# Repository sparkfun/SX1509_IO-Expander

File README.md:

SparkFun 16 Output I/O Expander Breakout - SX1509
======================================

[  
*SX1509 16 Output I/O Expander Breakout (BOB-13601)*](https://www.sparkfun.com/products/13601)

The SX1509 16 Output I/O Expander Breakout Board makes it easy to prototype using the SX1509 so you can add more I/O onto your Arduino or I/O limited controller. It can leverage your I2C interface for 16 extra channels of GPIO and contains a fully programmable LED driver and a keypad scanning engine which enables continuous keypad monitoring of up to 64 keys. Since the I/O banks can operate between 1.2V and 3.6V (5.5V tolerant) independent of both the core and each other, this device can also work as a level-shifter.

Features include:

* 16 channels of bi-directional I/O - Pull-up/down resistors, push/pull or open-drain outputs, programmable polarity.
* 5.5V tolerant I/O's (1.2-3.6V operating voltage)
* LED Driver: PWM and blink control on all I/O's, breathe capability on a select few.
* Level shifting I/O's: Independent I/O rails (VCC1, VCC2) allow for up/down level shifting.
* Keypad scanning engine: Supports up to 64 keys (in an 8x8 matrix configuration).

Repository Contents
-------------------
* **/Hardware** - Eagle design files (.brd, .sch)
* **/Libraries** - Libraries for use with the <PRODUCT NAME>
* **/Production** - Production panel files (.brd)

Documentation
--------------
* **[Library](https://github.com/sparkfun/SparkFun_SX1509_Arduino_Library)** - <LANGUAGE> library for the SX1509.
* **[Hookup Guide](https://learn.sparkfun.com/tutorials/sx1509-io-expander-breakout-hookup-guide?_ga=1.227875988.863167751.1453149924)** - Basic hookup guide for the SX1509.
* **[SparkFun Fritzing repo](https://github.com/sparkfun/Fritzing_Parts)** - Fritzing diagrams for SparkFun products.
* **[SparkFun 3D Model repo](https://github.com/sparkfun/3D_Models)** - 3D models of SparkFun products. 
* **[SparkFun Graphical Datasheets](https://github.com/sparkfun/Graphical_Datasheets)** -Graphical Datasheets for various SparkFun products.

Product Versions
-------------------

* [BOB-13601](https://www.sparkfun.com/products/13601) - SX1509 16 I/O Breakout Board (v20)
* [BOB-11502](https://www.sparkfun.com/products/retired/11502)- (Retired) SX1509 16 I/O I2C port expander (v10)

License Information
-------------------
This product is _**open source**_! 

The **hardware** is released under [Creative Commons ShareAlike 4.0 International](https://creativecommons.org/licenses/by-sa/4.0/).

The **code** is beerware; if you see me (or any other SparkFun employee) at the local, and you've found our code helpful, please buy us a round!

Please use, reuse, and modify these files as you see fit. Please maintain attribution to SparkFun Electronics and release anything derivative under the same license.

Distributed as-is; no warranty is given.

- Your friends at SparkFun.

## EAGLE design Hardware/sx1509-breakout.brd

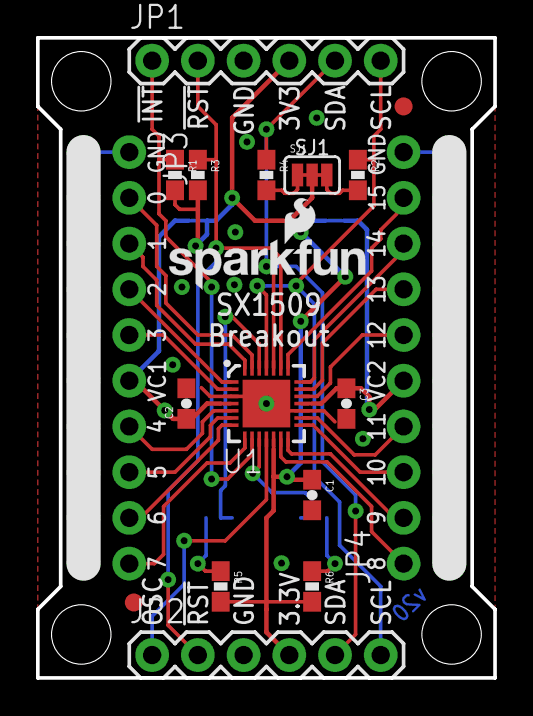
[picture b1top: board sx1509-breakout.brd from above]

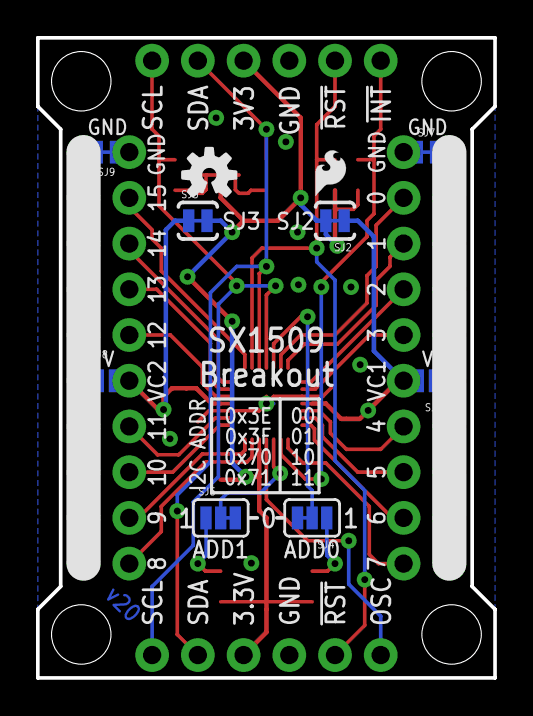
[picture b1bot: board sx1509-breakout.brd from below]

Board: 2 copper layers, 25.4 x 35.6 mm, 33 parts (10 on the bottom side), 33 nets.

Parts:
C1, C2, C3: 0.1uF; 0603-CAP
FRAME1: CREATIVE_COMMONS
JP1, JP2: 1X06
JP3, JP4: 2X10_ROUND_NOSILK
JP9, JP10: FIDUCIAL1X2; FIDUCIAL-1X2
LOGO1: SFE_LOGO_NAME_FLAME.1_INCH; SFE_LOGO_NAME_FLAME_.1
LOGO2: SFE_LOGO_FLAME.1_INCH; SFE_LOGO_FLAME_.1
LOGO3: OSHW-LOGOS; OSHW-LOGO-S
R1, R2, R3, R4, R5, R6: 10K; 0603-RES
SJ1: PAD-JUMPER-3-3OF3_NC_BY_TRACE_YES_SILK_FULL_BOX
SJ2: VCC1-3.3V; PAD-JUMPER-2-NC_BY_TRACE_YES_SILK
SJ3: VCC2-3.3V; PAD-JUMPER-2-NC_BY_TRACE_YES_SILK
SJ4, SJ5: PAD-JUMPER-3-2OF3_NC_BY_TRACE_YES_SILK_FULL_BOX
SJ6: A-VCC1; PAD-JUMPER-2-NO_NO_SILK
SJ7, SJ9: GND; PAD-JUMPER-2-NC_BY_TRACE_NO_SILK
SJ8: B-VCC2; PAD-JUMPER-2-NO_NO_SILK
STANDOFF1, STANDOFF2, STANDOFF3, STANDOFF4: STAND-OFF
U1: SX1509; QFN-28

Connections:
0: JP3.4, U1.27
1: JP3.6, U1.28
2: JP3.8, U1.1
3: JP3.10, U1.2
3.3V: C1.1, JP1.4, JP2.4, R1.2, R3.2, R5.2, R6.2, SJ1.2, SJ2.2, SJ3.2, U1.12
4: JP3.14, U1.5
5: JP3.16, U1.6
6: JP3.18, U1.7
7: JP3.20, U1.8
8: JP4.2, U1.13
9: JP4.4, U1.14
10: JP4.6, U1.15
11: JP4.8, U1.16
12: JP4.12, U1.19
13: JP4.14, U1.20
14: JP4.16, U1.21
15: JP4.18, U1.22
!INT: JP1.1, R1.1, U1.9
!RESET: JP1.2, JP2.2, R3.1, U1.23
ADDR0: SJ4.2, U1.26
ADDR1: SJ5.2, U1.10
GND: C1.2, C2.2, C3.2, JP1.3, JP2.3, JP3.2, JP4.20, SJ4.3, SJ5.3, SJ7.1, SJ9.1, U1.3, U1.17, U1.29
unnamed: R2.2, SJ1.3
unnamed: R4.2, SJ1.1
unnamed: JP4.1, JP4.3, JP4.5, JP4.7, JP4.9, JP4.11, JP4.13, JP4.15, JP4.17, JP4.19, SJ8.1, SJ9.2
unnamed: R5.1, SJ4.1
unnamed: R6.1, SJ5.1
OSCIO: JP2.1, U1.11
PWRBUSA: JP3.1, JP3.3, JP3.5, JP3.7, JP3.9, JP3.11, JP3.13, JP3.15, JP3.17, JP3.19, SJ6.1, SJ7.2
SCL: JP1.6, JP2.6, R2.1, U1.25
SDA: JP1.5, JP2.5, R4.1, U1.24
VCC1: C2.1, JP3.12, SJ2.1, SJ6.2, U1.4
VCC2: C3.1, JP4.10, SJ3.1, SJ8.2, U1.18

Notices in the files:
parts and their libraries:
SparkFun-DigitalIC: Licensing: CC v3.0 Share-Alike You are welcome to use this library for commercial purposes.
SparkFun-Aesthetics: Released under the Creative Commons Attribution Share-Alike 4.0 License
